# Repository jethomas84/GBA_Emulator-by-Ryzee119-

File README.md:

# GBA_Emulator-by-Ryzee119-

This was designed by /u/Ryzee
Originally posted on Reddit here:
https://www.reddit.com/r/DIY/comments/4zbqwr/this_is_my_attempt_at_making_a_portable_emulator/

Build Photos:
http://imgur.com/a/kjFmS

I am releasing these design files in good faith that people will use them to learn something about electronics and maybe bring an old Gameboy Advance (GBA) back to life.

I don’t want to see people taking this design and knocking it off for a quick buck.
If you don’t want to deal with all this work another redditor /u/Flav0r has designed something quite similar to this. http://gamepieadvance.com/ I understand he may be working on DIY Kits.

##DISCLAIMER:
This project is NOT for the fresh beginner or the faint of heart. It requires moderate/high level soldering skills. There are many small and fine pitch components that need to be soldered. I recommend you don’t attempt this unless you have experience in soldering, a basic ability to troubleshoot electronic circuits if things aren’t working and an ability to make mods on the fly to suit your needs. i.e cutting plastic where required.
This also requires taking apart an original GBA to repurpose the case, buttons and de-soldering of several components on the GBA motherboard. This can very tricky without the right equipment.
As a minimum the following tools are recommended (All parts should be of good quality from reputable suppliers!):

1.	A decent temperature controlled soldering station with suitable tips for fine work
2.	Solder flux
3.	Leaded solder
4.	Fine tweezers (anti-magnetic)
5.	Solder wick
6.	Multimeter for testing

This is a **FIRST PROTOTYPE** board which just happened to work reasonably ok. This has not undergone any extensive testing.

I take no responsibility for the following:

1.	You went ahead and purchased everything, soldered it up and it didn’t work.
2.	You soldered an SMD chip and bent and broke the pins.
3.	If a component in the BOM is not available or becomes obsolete, use your best judgement to find a replacement.
4.	A component was missing from the BOM. (I did check it. But it’s your responsibility to check it again against the schematic)
5.	The thing burst into flame and explodes in your hands and burns your house down.
6.	It doesn’t fit in your GBA case. (It was designed to one I had lying around. I don’t know if Nintendo did subtle changes in their cases over the years)
7.	Hours of lost productivity because you're slaying bosses and saving princesses.

Any advice and support I provide from this point is purely out of the kindness of my heart.

## ISSUES OBSERVED WITH THE BOARD:
Again, this is a first prototype. I have observed the following issues:

1. Slight buzzing from the speaker. More noticeable when volume is high and no sound is being played. I’ve added some extra decoupling caps to the area but this may or may not do a thing.

2. DC boost converter struggles at low input voltages. Although I tried to design it for this; if you use Alkaline batteries you will probably be disappointed. Once the input voltage drops below ~2.5V expect the random reboot at high loads. I recommend good quality Lithium AA batteries. Because of lithium discharge curves, the low battery indictor circuit is not particularly useful.

3. The closest screen I could find to the original is a 3.2" TFT. It is slightly bigger than the viewing window. The left and bottom edges of the screen are cut off slightly. Borders can be setup in RetroArch so the games don't have this issue, however it is visible in the game selection screens.

4. Probably more. This has not been extensively tested.

## Controls
So if you managed to get everything up and running. Congrats! If you followed the software setup guide it has the following key combos setup:

1. SELECT+START = Exit current rom
2. SELECT+A = Save current state
3. SELECT+B = Load current state
4. SELECT+RIGHT SHOULDER = High speed
5. SELECT+LEFT SHOULDER = Rewind gameplay around 3-4 seconds
6. SELECT+LEFT/RIGHT = INCREASE/DECREASE Screen brightness

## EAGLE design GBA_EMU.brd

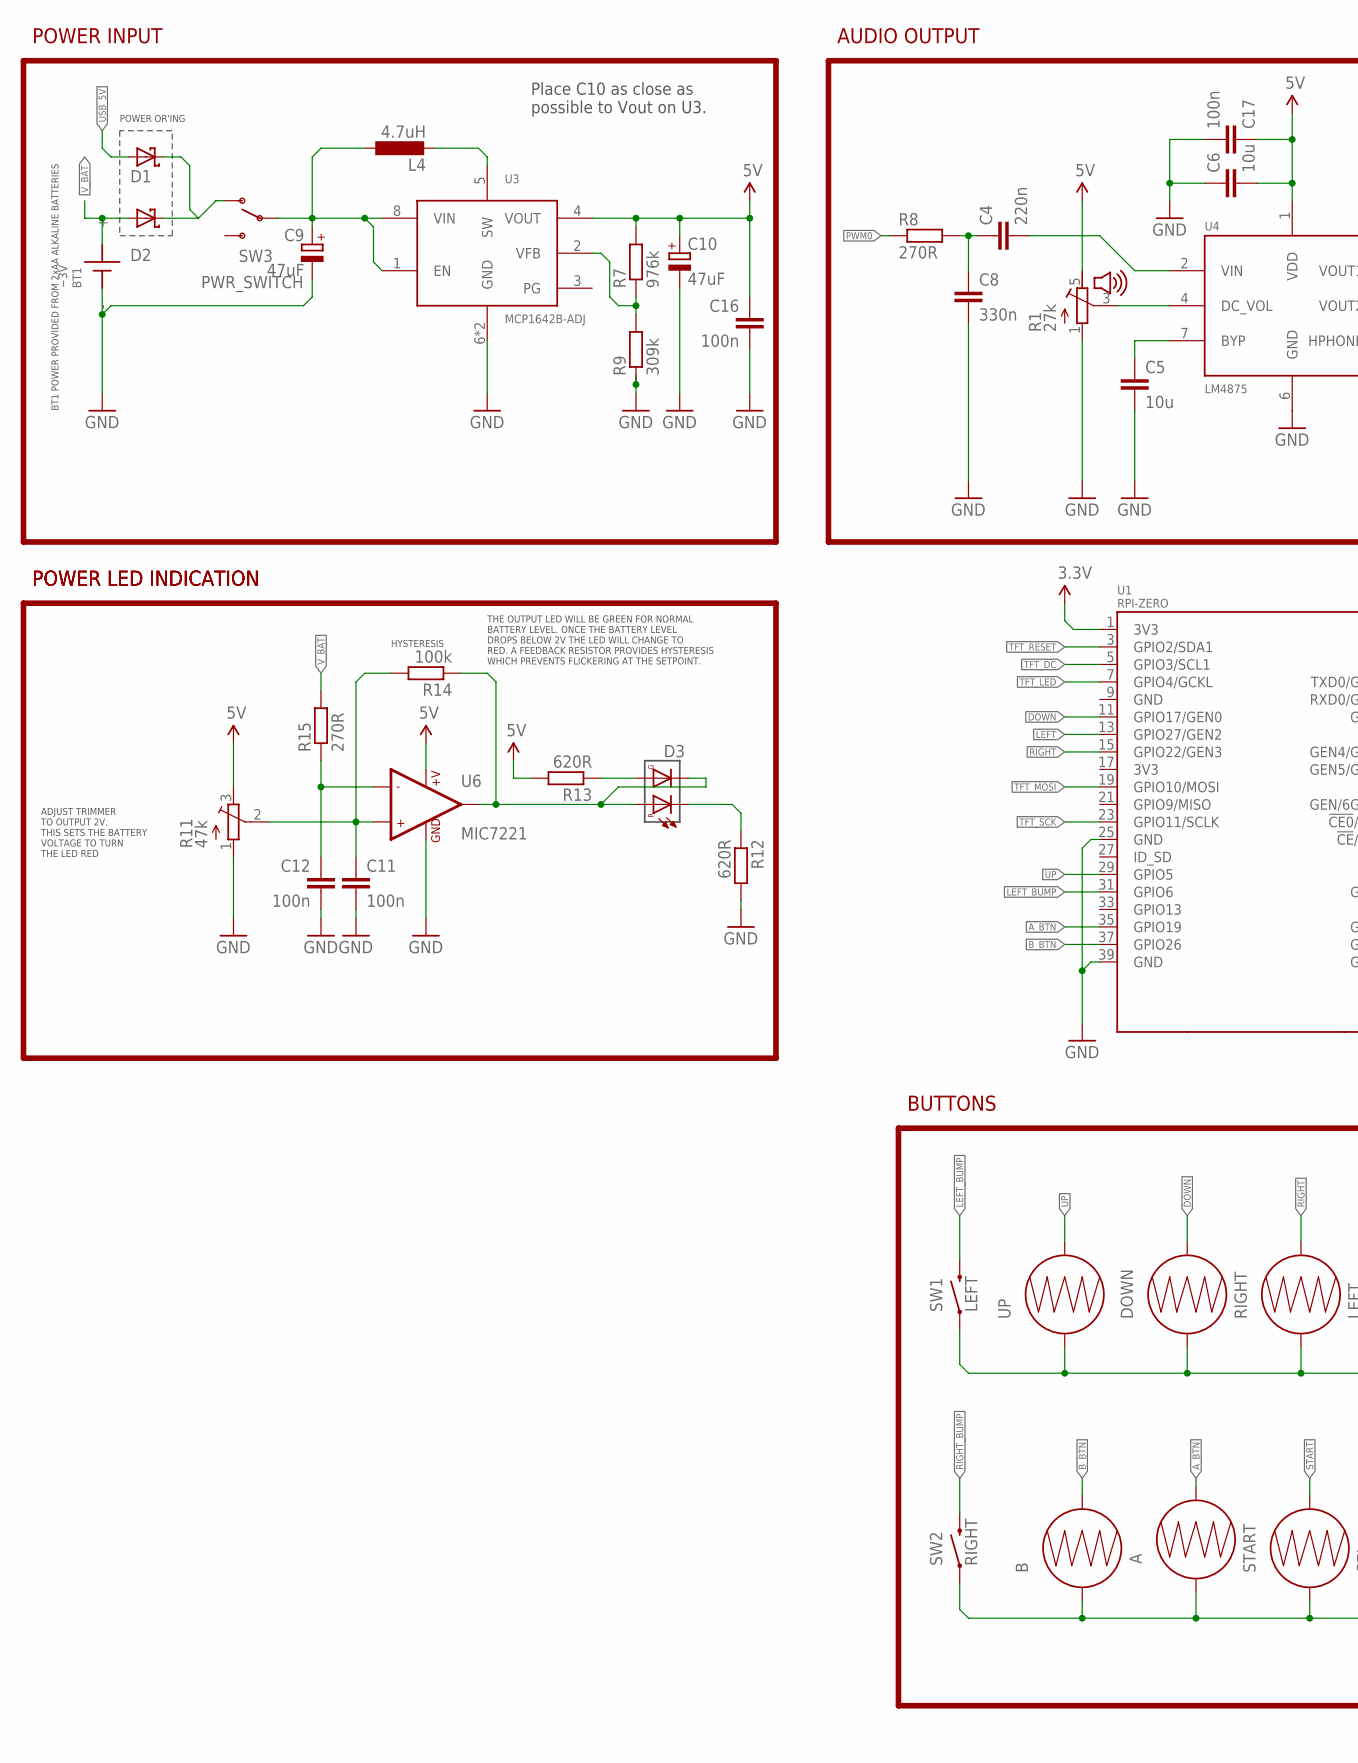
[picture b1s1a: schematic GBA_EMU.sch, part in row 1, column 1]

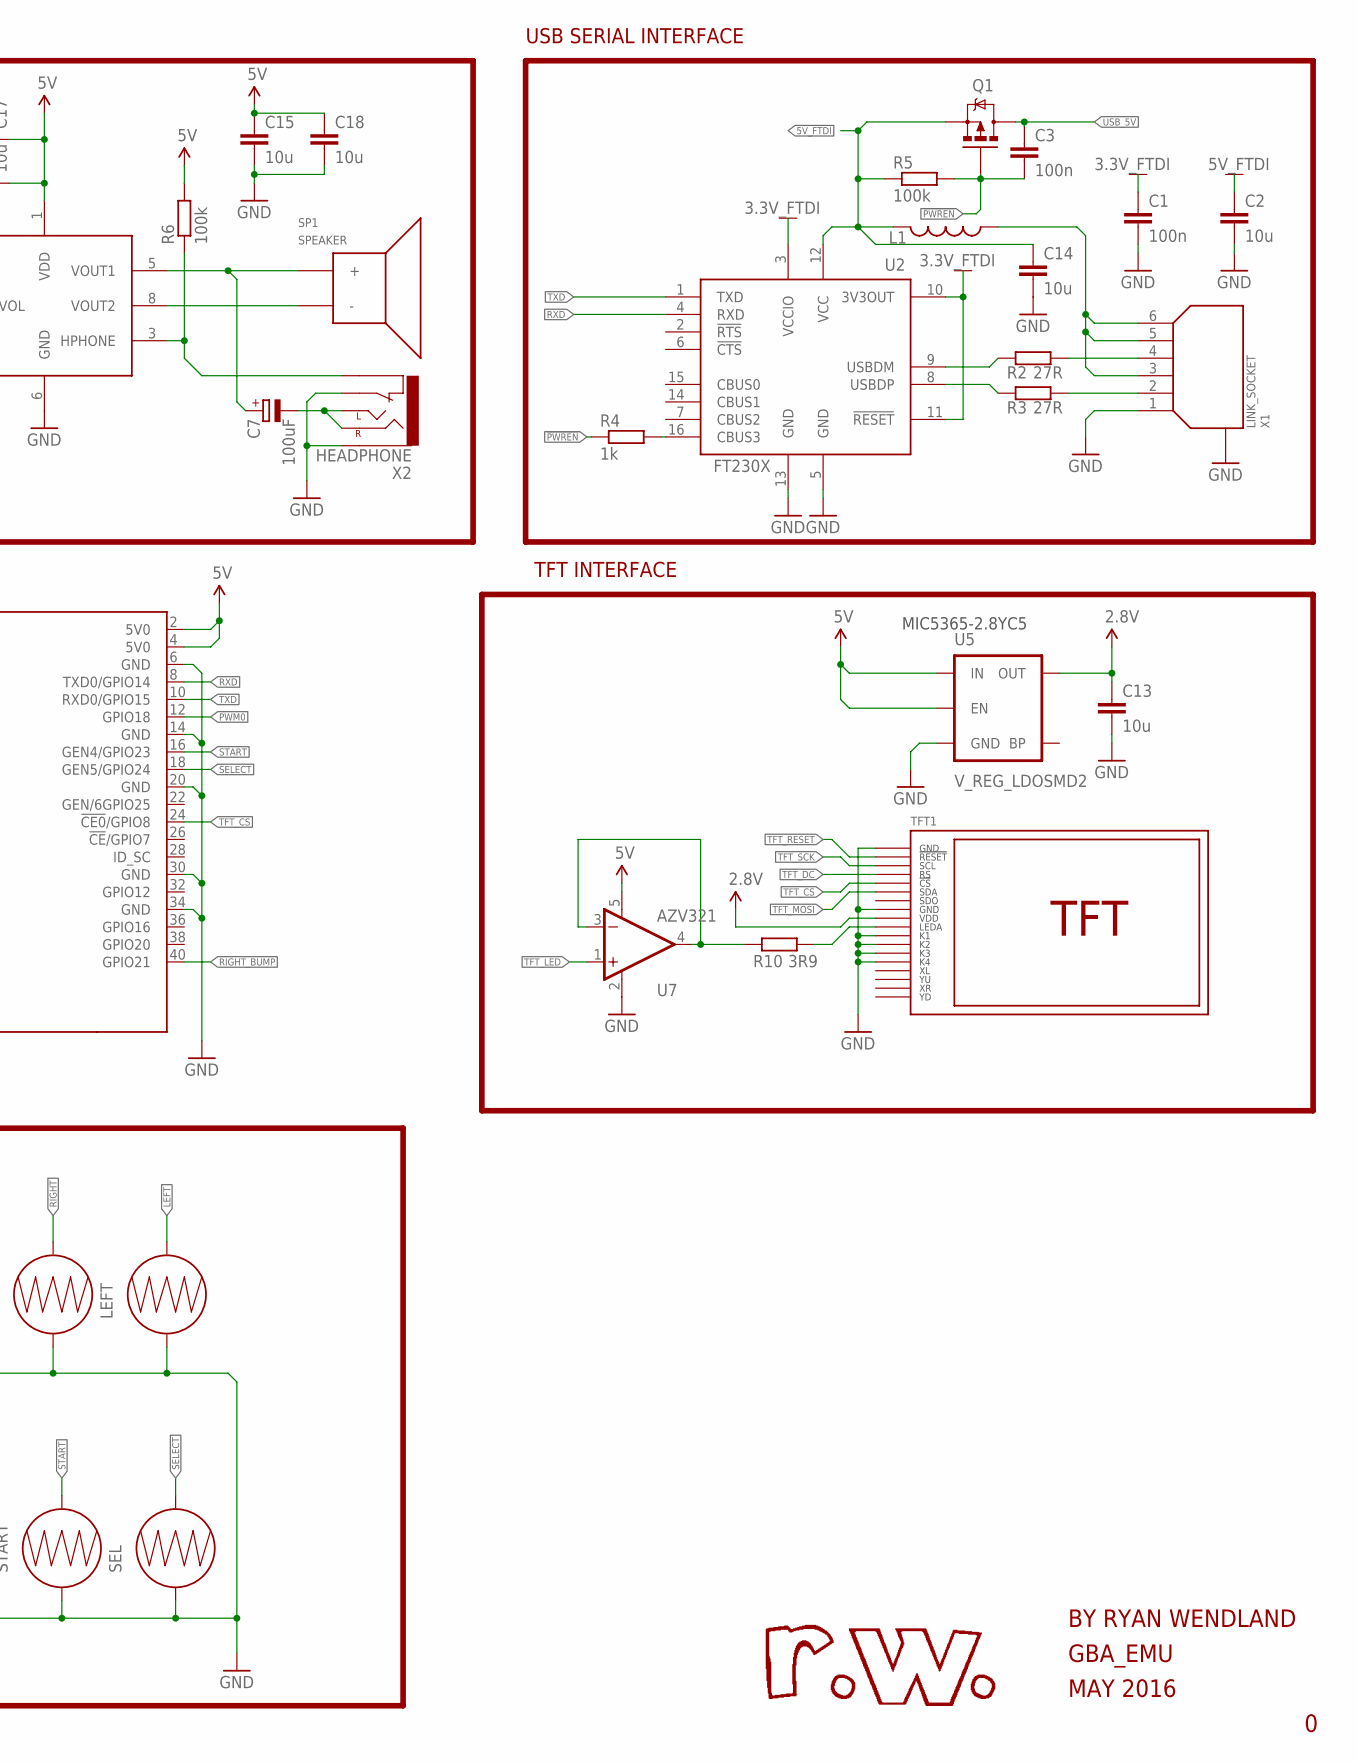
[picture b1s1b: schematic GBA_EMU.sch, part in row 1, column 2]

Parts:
A: GBA_BTN_CONDUCTIVE; GBA_BUTTON_CONDUCTIVE
B: GBA_BTN_CONDUCTIVE; GBA_BUTTON_CONDUCTIVE
BT1: ~3V; BATTERY
C1, C3, C11, C12, C16, C17: 100n; C0805
C2, C5, C6, C13, C14, C15, C18: 10u; C0805
C4: 220n; C0805
C7: 100uF; 153CLV-0405
C8: 330n; C0805
C9, C10: 47uF; 153CLV-0405
D1, D2: DFLS130L; POWERDI_123
D3: DUAL_LED
DOWN: GBA_BTN_CONDUCTIVE; GBA_BUTTON_CONDUCTIVE
L1: 600; 0805
L4: 4.7uH; POWER-CHOKE_WE-TPC
LEFT: GBA_BTN_CONDUCTIVE; GBA_BUTTON_CONDUCTIVE
Q1: MOSFET-PCHANNEL; SOT23-3
R1: 27k; VOLUME
R2, R3: 27R; R0805
R4: 1k; R0805
R5, R6, R14: 100k; R0805
R7: 976k; R0805
R8, R15: 270R; R0805
R9: 309k; R0805
R10: 3R9; R0805
R11: 47k; TC33X
R12, R13: 620R; R0805
RIGHT: GBA_BTN_CONDUCTIVE; GBA_BUTTON_CONDUCTIVE
SEL: BUTTON-CONDUCTIVESMD; BUTTON-CONDUCTIVE
SP1: SPEAKER
START: BUTTON-CONDUCTIVESMD; BUTTON-CONDUCTIVE
SW1: LEFT; BUMPER
SW2: RIGHT; BUMPER
SW3: PWR_SWITCH
TFT1: GBA_TFT
U1: RPI-ZERO; RASPBERRYPI_BASTELSTUBE_V13_RASPI_BOARD_B+_FULL
U2: FT230X; SSOP16
U3: MCP1642B-ADJ; MSOP8
U4: LM4875; SOIC8
U5: V_REG_LDOSMD2; SC70
U6: MIC7221; SOT23-5
U7: AZV321; SOT23-5
UP: GBA_BTN_CONDUCTIVE; GBA_BUTTON_CONDUCTIVE
X1: LINK_SOCKET
X2: HEADPHONE

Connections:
0.8128: C9.+, L4.1, SW3.COM1, SW3.COM2, U3.1 (EN), U3.8 (VIN)
2.8V: C13.1, TFT1.9 (VDD), U5.5 (OUT)
3.3V: U1.1 (3V3)
3.3V_FTDI: C1.1, U2.3 (VCCIO), U2.10 (3V3OUT), U2.11 (!RESET)
5V: C6.2, C10.+, C15.1, C16.1, C17.1, C18.1, R1.5 (E), R6.2, R7.2, R11.3 (E), R13.2, U1.2 (5V0), U1.4 (5V0), U3.4 (VOUT), U4.1 (VDD), U5.1 (IN), U5.3 (EN), U6.2 (+V), U7.5 (V+)
5V_FTDI: C2.1, C14.1, L1.1, Q1.2 (S), R5.1, U2.12 (VCC)
!PWREN: C3.2, Q1.1 (G), R4.1, R5.2
A_BTN: A.2, U1.35 (GPIO19)
B_BTN: B.2, U1.37 (GPIO26)
DOWN: DOWN.2, U1.11 (GPIO17/GEN0)
GND: A.1, B.1, BT1.BT-1 (-), BT1.BT-2 (-), C1.2, C2.2, C5.2, C6.1, C8.2, C9.-, C10.-, C11.2, C12.2, C13.2, C14.2, C15.2, C16.2, C17.2, C18.2, DOWN.1, LEFT.1, R1.1 (A), R9.1, R11.1 (A), R12.2, RIGHT.1, SEL.1, START.1, SW1.1, SW2.1, TFT1.1 (GND), TFT1.8 (GND), TFT1.11 (K1), TFT1.12 (K2), TFT1.13 (K3), TFT1.14 (K4), U1.6 (GND), U1.14 (GND), U1.20 (GND), U1.25 (GND), U1.30 (GND), U1.34 (GND), U1.39 (GND), U2.5 (GND), U2.13 (GND), U3.6 (GND), U3.7 (GND), U4.6 (GND), U5.2 (GND), U6.5 (GND), U7.2 (V-), UP.1, X1.1, X1.GND@1 (GND), X1.GND@2 (GND), X2.1, X2.GND
LEFT: LEFT.2, U1.13 (GPIO27/GEN2)
LEFT_BUMP: SW1.2, U1.31 (GPIO6)
unnamed: C11.1, R11.2 (S), R14.2, U6.3 (+IN1)
unnamed: C4.1, C8.1, R8.2
unnamed: L1.2, X1.3, X1.5, X1.6
unnamed: R2.2, X1.4
unnamed: R3.2, X1.2
unnamed: R2.1, U2.9 (USBDM)
unnamed: R3.1, U2.8 (USBDP)
unnamed: R1.3 (S), U4.4 (DC_VOL)
unnamed: C4.2, U4.2 (VIN)
unnamed: R4.2, U2.16 (CBUS3)
unnamed: C5.1, U4.7 (BYP)
unnamed: L4.2, U3.5 (SW)
unnamed: C7.-, X2.L (LEFT), X2.R (RIGHT)
unnamed: C7.+, SP1.1 (+), U4.5 (VOUT1)
unnamed: SP1.2 (-), U4.8 (VOUT2)
unnamed: R6.1, U4.3 (HPHONE), X2.2
unnamed: D1.2 (C), D2.2 (C), SW3.1 (O)
unnamed: D3.1, D3.3, R14.1, U6.1 (OUT1)
unnamed: R7.1, R9.2, U3.2 (VFB)
unnamed: R10.2, TFT1.10 (LEDA)
unnamed: D3.4, R13.1
unnamed: D3.2, R12.1
unnamed: R10.1, U7.3 (-IN), U7.4 (OUT)
unnamed: C12.1, R15.1, U6.4 (-IN1)
PWM0: R8.1, U1.12 (GPIO18)
RIGHT: RIGHT.2, U1.15 (GPIO22/GEN3)
RIGHT_BUMP: SW2.2, U1.40 (GPIO21)
RXD: U1.8 (TXD0/GPIO14), U2.4 (RXD)
SELECT: SEL.2, U1.18 (GEN5/GPIO24)
START: START.2, U1.16 (GEN4/GPIO23)
TFT_CS: TFT1.5 (!CS), U1.24 (!CE0!/GPIO8)
TFT_DC: TFT1.4 (RS), U1.5 (GPIO3/SCL1)
TFT_LED: U1.7 (GPIO4/GCKL), U7.1 (+IN)
TFT_MOSI: TFT1.6 (SDA), U1.19 (GPIO10/MOSI)
TFT_RESET: TFT1.2 (!RESET), U1.3 (GPIO2/SDA1)
TFT_SCK: TFT1.3 (SCL), U1.23 (GPIO11/SCLK)
TXD: U1.10 (RXD0/GPIO15), U2.1 (TXD)
UP: U1.29 (GPIO5), UP.2
USB_5V: C3.1, D1.1 (A), Q1.3 (D)
V_BAT: BT1.BT+1 (+), BT1.BT+2 (+), D2.1 (A), R15.2

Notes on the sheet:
USB SERIAL INTERFACE
AUDIO OUTPUT
POWER INPUT
POWER OR'ING
BT1 POWER PROVIDED FROM 2xAA ALKALINE BATTERIES
TFT INTERFACE
ADJUST TRIMMER TO OUTPUT 2V. THIS SETS THE BATTERY VOLTAGE TO TURN THE LED RED
HYSTERESIS
POWER LED INDICATION
THE OUTPUT LED WILL BE GREEN FOR NORMAL BATTERY LEVEL. ONCE THE BATTERY LEVEL DROPS BELOW 2V THE LED WILL CHANGE TO RED. A FEEDBACK RESISTOR PROVIDES HYSTERESIS WHICH PREVENTS FLICKERING AT THE SETPOINT.
GBA_EMU
MAY 2016
BY RYAN WENDLAND
BUTTONS
Place C10 as close as possible to Vout on U3.
MIC5365-2.8YC5

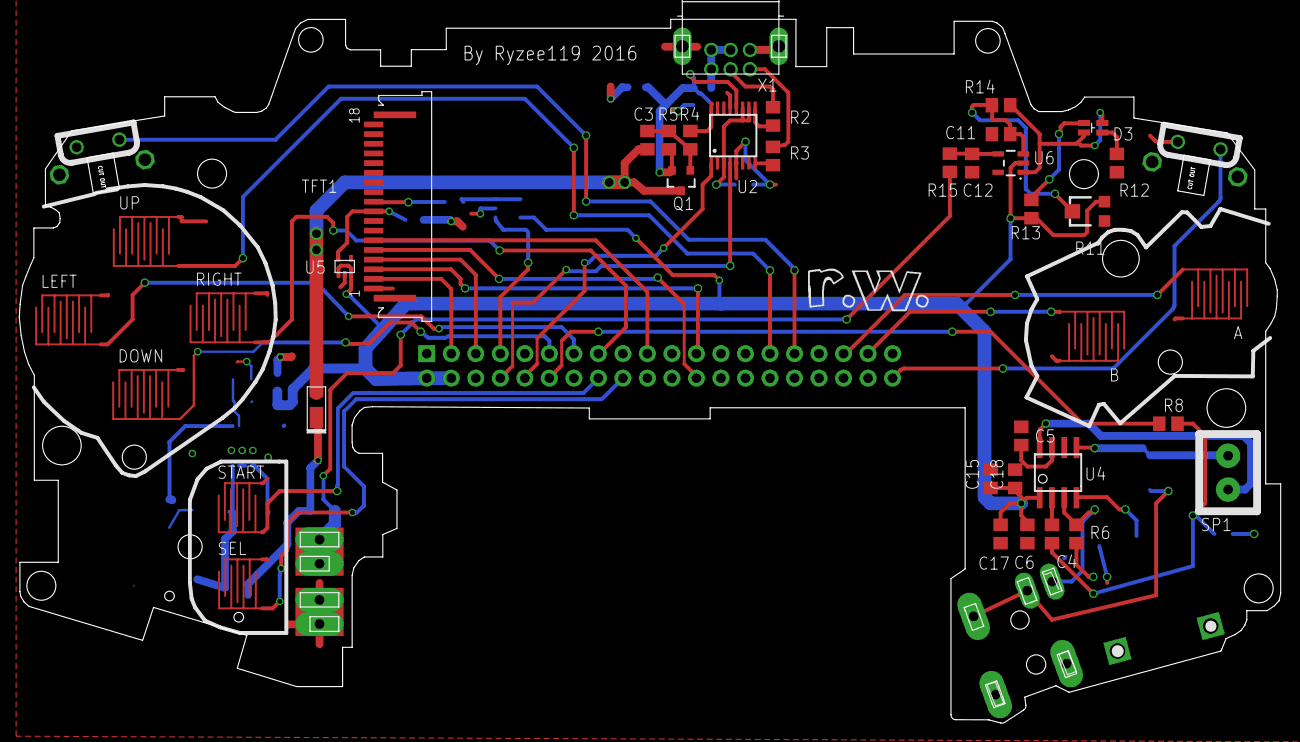
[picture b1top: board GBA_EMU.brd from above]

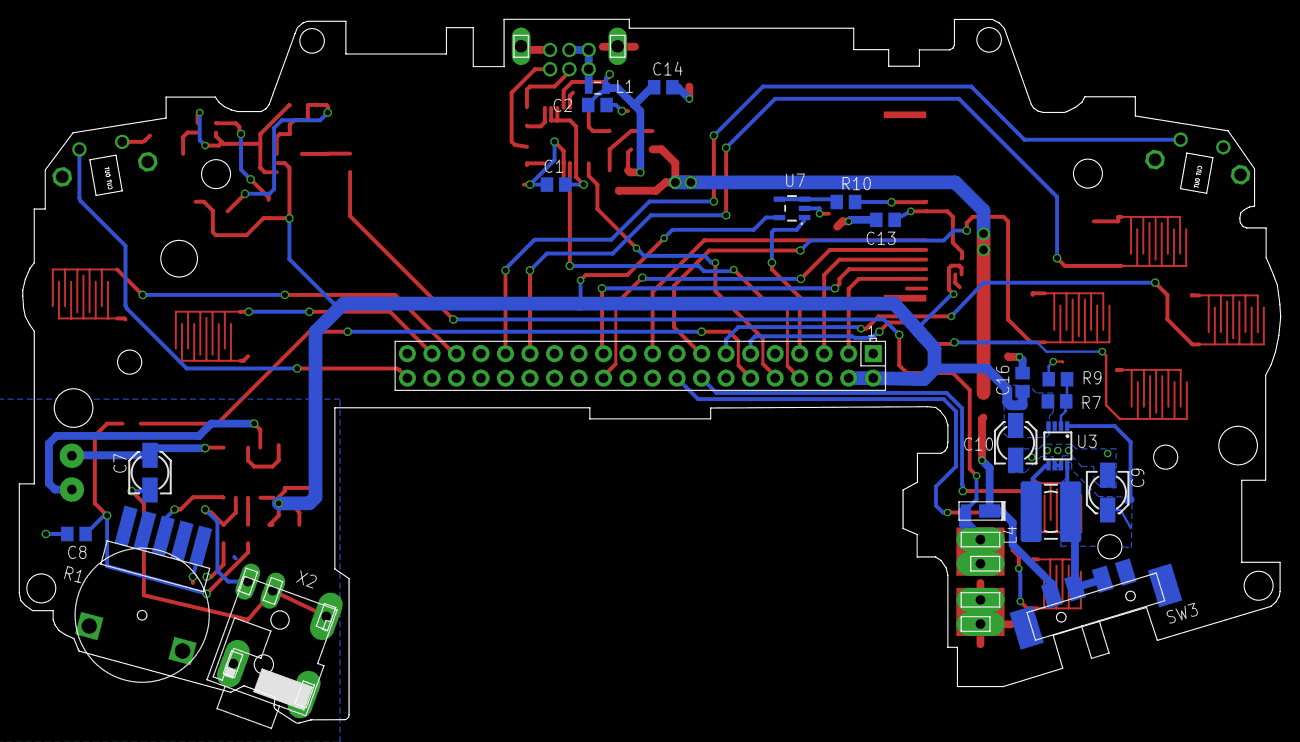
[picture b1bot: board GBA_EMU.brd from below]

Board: 2 copper layers, 130.7 x 72.9 mm, 62 parts (21 on the bottom side), 52 nets.

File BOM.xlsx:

|  | Bill of Materials based on my GBA mod. By /u/Ryzee http://imgur.com/a/kjFmS htt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 | Build at your own risk!
Qty | Value | Device | Parts | Digikey part
3 | 100k | RES SMD 100K OHM 1% 1/8W 0805 | R5, R6, R14 | RMCF0805FT100KCT-ND
6 | 100n | CAP CER 0.1UF 25V X7R 0805 | C1, C3, C11, C12, C16, C17 | 1276-1099-1-ND
7 | 10u | CAP ALUM 10UF 20% 16V SMD | C2, C5, C6, C13, C14, C15, C18 | 493-2100-1-ND
1 | 1k | RES SMD 1K OHM 1% 1/8W 0805 | R4 | RMCF0805FT1K00CT-ND
1 | 220n | CAP CER 0.22UF 16V X7R 0805 | C4 | 1276-1284-1-ND
2 | 270R | RES SMD 270 OHM 1% 1/8W 0805 | R8, R15 | RMCF0805FT270RCT-ND
2 | 27R | RES SMD 27 OHM 1% 1/8W 0805 | R2, R3 | RMCF0805FT27R0CT-ND
1 | 430k | RES SMD 430K OHM 1% 1/8W 0805 | R9 | P430KCCT-ND
1 | 330n | CAP CER 0.33UF 50V X7R 0805 | C8 | 1276-1123-1-ND
1 | 3R9 | RES SMD 3.9 OHM 1% 1/8W 0805 | R10 | RMCF0805FT3R90CT-ND
1 | 4.7uH | FIXED IND 4.7UH 1.72A 82 MOHM | L4 | 732-1021-1-ND
1 | 47k | PVZ3A473C01R00 | R11 (Use 10K version if out of stock) | 490-7795-1-ND
3 | 47uF | CAP ALUM 47UF 20% 16V SMD | C9, C10 | P15090CT-ND
1 | 600 Ohm | FERRITE BEAD 600 OHM 0805 1LN | L1 | 240-2390-1-ND
2 | 620R | RES SMD 620 OHM 1% 1/8W 0805 | R12, R13 | 1276-5260-1-ND
1 | 976k | RES 976K OHM 1/8W 1% 0805 | R7 | 311-976KCRCT-ND
1 | AZV321 | IC OPAMP GEN PURP SOT25 | U7 | AZV321KTR-G1DICT-ND
2 | DFLS130L | DIODE SCHOTTKY 30V 1A POWERDI123 | D1, D2 | DFLS130LDICT-ND
1 | XZMDKVG54W-4 | LED GREEN/RED DUAL LED CLEAR 0805 SMD | D3 | 1497-1182-1-ND
1 | FT230X | IC USB SERIAL BASIC UART 16SSOP | U2 | 768-1154-5-ND
1 | LM4875 | IC AMP AUDIO PWR 1W MONO 8SOIC | U4 | 296-35282-1-ND
1 | MCP1642B-ADJ | IC REG BOOST ADJ 0.8A SYNC 8MSOP | U3 | MCP1642B-ADJI/MS-ND
1 | MIC7211 | IC COMPARATOR R-R INPUT SOT23-5 | U6 | 576-1318-1-ND
1 | IRLML6401TRPBF | MOSFET P-CH 12V 4.3A SOT-23 | Q1 | IRLML6401PBFCT-ND
1 | CLS0231MA-1-L152 | SPEAKER 8OHMS .5W 23MM 6" LEADS | SP1 | 102-1553-ND
1 | MIC5365-2.8YC5-TR | IC REG LDO 2.8V 0.15A SC70-5 | U5 | 576-3187-1-ND
1 | FLAT FLEX | HF18U-02-ND CABLE FLAT FLEX 18POS 1MM 2" | - | HF18U-02-ND
1 | GBA_TFT_CON | CONN FFC BOTTOM 18POS 1.00MM R/A | TFT1 | 609-1911-1-ND
1 | TFT DISPLAY | 3.2" 18P SPI TFT ILI9341 320x240 | - | Aliexpress
1 | 27k | Nintendo VOLUME ADJUST POT | R1 | Taken out of old GBA
1 | HEADPHONE | Nintendo HEADPHONE | X2 | Taken out of old GBA
2 | L+R SHOULDER | Nintendo BUTTON | SW1 | Taken out of old GBA
1 | LINK_SOCKET | Nintendo LINK_SOCKET | X1 | Taken out of old GBA
1 | PWR_SWITCH | Nintendo PWR_SWITCH | SW3 | Taken out of old GBA
1 | RPI-ZERO | RPI-ZERO | U1 | -
2 | AA Batteries | Recommendation is ENERGIZER L91 Lithium or equivalent good quality lithium AA's |  | -
1 | GBA Link cable | Needs to be modified with a USB male connector on one end |  | eBay
1 | TFT_ADAPTER_PCB | ADAPTER PCB FOR TFT FLAT FLEX CABLE | - | OHSPark Direct Link
NOTE: THESE ARE ALL BARE MINIMUM QUANTITIES. I RECOMMEND GETTING SPARES BECAUSE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

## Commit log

2016-08-26 Create Will be here soon
2016-08-27 Create FAQ
2016-08-27 Changed R9 to 430k.
2016-08-28 Create retrogame.c
    Modified version from https://github.com/adafruit/Adafruit-Retrogame
2016-08-28 Makefile for retrogame.c
    Execute with 'make retrogame'
2016-08-28 Device tree overlay for TFT

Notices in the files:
parts and their libraries:
SparkFun-Electromechanical: Licensing: Creative Commons ShareAlike 4.0 International - https://creativecommons.org/licenses/by-sa/4.0
